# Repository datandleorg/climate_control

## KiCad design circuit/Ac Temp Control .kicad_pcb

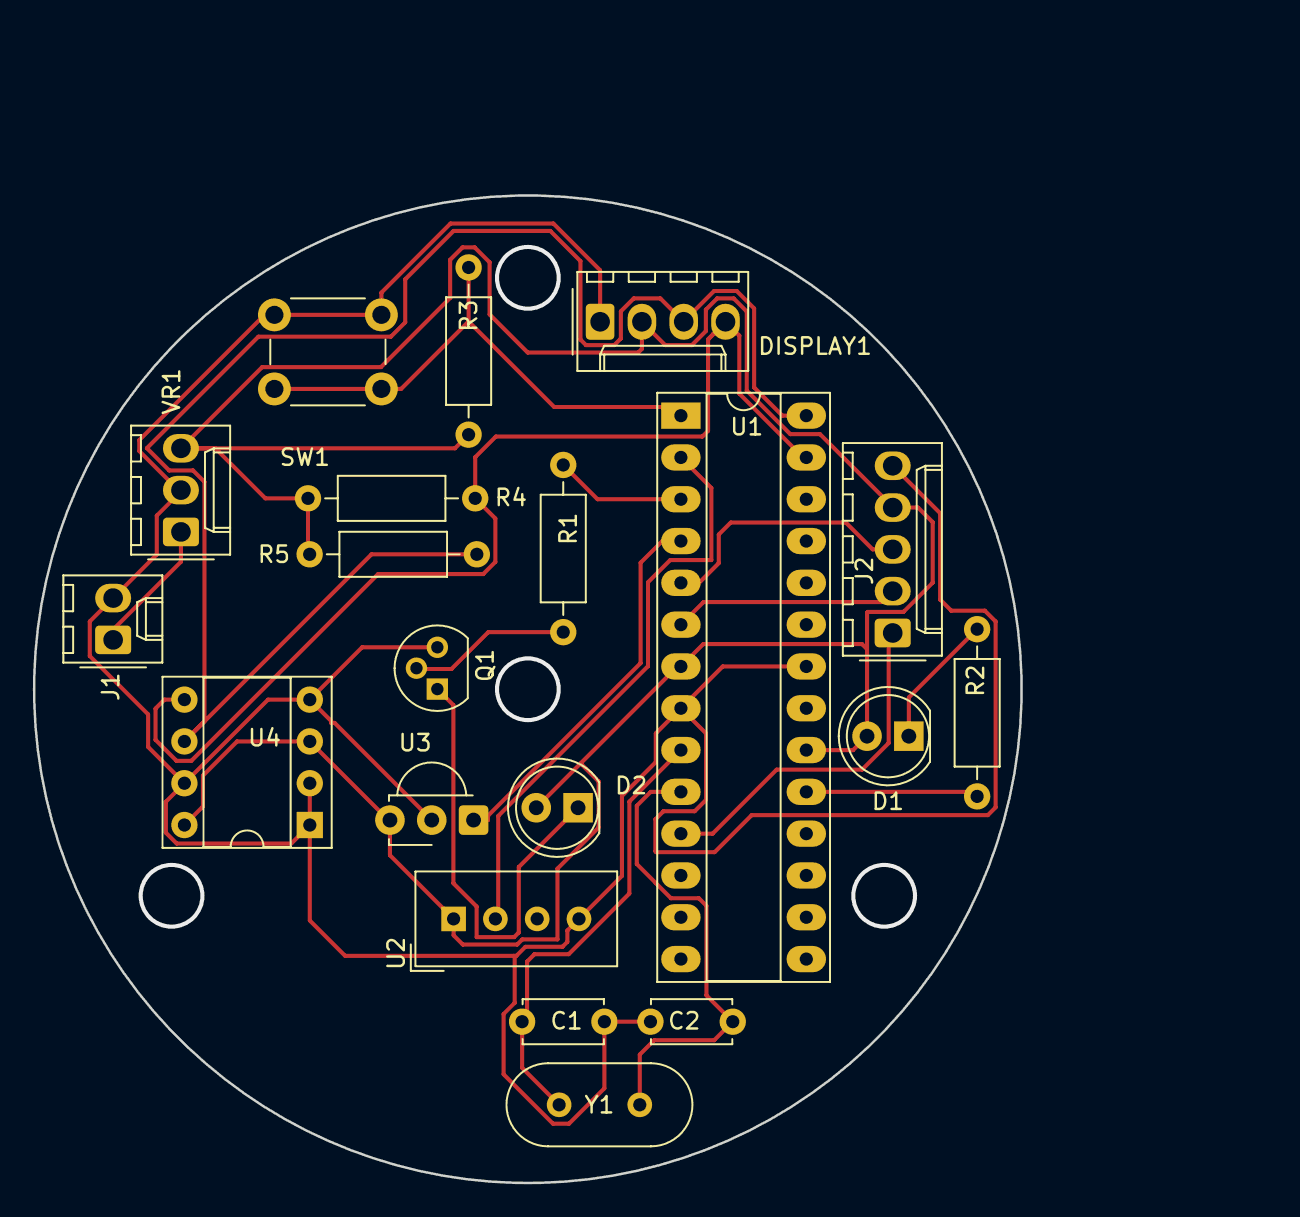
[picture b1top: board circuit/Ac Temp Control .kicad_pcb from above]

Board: 2 copper layers, 74.8 x 69.8 mm, 20 parts (0 on the bottom side), 18 nets.

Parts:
C1, C2: 22UF; C_Disc_D4.7mm_W2.5mm_P5.00mm
D1: LED; LED_D5.0mm
D2: IR_EMITTER; LED_D5.0mm
DISPLAY1: SSD1306; Molex_KK-254_AE-6410-04A_1x04_P2.54mm_Vertical
J1: Conn_01x02_Male; Molex_KK-254_AE-6410-02A_1x02_P2.54mm_Vertical
J2: Conn_01x05_Male; Molex_KK-254_AE-6410-05A_1x05_P2.54mm_Vertical
Q1: P2N2222A; TO-92
R1: 470; R_Axial_DIN0207_L6.3mm_D2.5mm_P10.16mm_Horizontal
R2, R3: 100; R_Axial_DIN0207_L6.3mm_D2.5mm_P10.16mm_Horizontal
R4, R5: 4.7k; R_Axial_DIN0207_L6.3mm_D2.5mm_P10.16mm_Horizontal
SW1: SW_Push; SW_PUSH_6mm
U1: ATmega328-P; DIP-28_W7.62mm_Socket_LongPads
U2: DHT11; Aosong_DHT11_5.5x12.0_P2.54mm
U3: TSOP382xx; Vishay_MINICAST-3Pin
U4: CAT24C256; DIP-8_W7.62mm_Socket
VR1: L7805; Molex_KK-254_AE-6410-03A_1x03_P2.54mm_Vertical
Y1: 16MHZ; Crystal_HC18-U_Vertical

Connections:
GND: C1.2, C2.2, DISPLAY1.1 (GND), J1.2, J2.5, Q1.3 (E), SW1.1, U1.8 (GND), U1.22 (GND), U2.4 (GND), U3.2 (GND), U4.1 (A0), U4.2 (A1), U4.4 (GND), U4.7 (WP), VR1.2 (GND)
unnamed: C1.1, U1.9 (XTAL1/PB6), Y1.1
unnamed: C2.1, U1.10 (XTAL2/PB7), Y1.2
unnamed: D1.1 (K), R2.1
unnamed: D1.2 (A), D2.2, DISPLAY1.2 (VCC), J2.4, R3.2, R4.2, R5.2, U1.7 (VCC), U1.20 (AVCC), U2.1 (VCC), U3.3 (Vs), U4.3 (A2), U4.8 (VCC), VR1.3 (OUT)
unnamed: D2.1, Q1.1 (C)
unnamed: DISPLAY1.3 (SCL), R5.1, U1.28 (PC5), U4.6 (SCL)
unnamed: DISPLAY1.4 (SDA), R4.1, U1.27 (PC4), U4.5 (SDA)
unnamed: J1.1, VR1.1 (IN)
unnamed: J2.1, U1.11 (PD5)
unnamed: J2.2, U1.6 (PD4)
unnamed: J2.3, U1.5 (PD3)
unnamed: Q1.2 (B), R1.2
unnamed: R1.1, U1.3 (PD1)
unnamed: R2.2, U1.19 (PB5)
unnamed: R3.1, SW1.2, U1.1 (~RESET/PC6)
unnamed: U1.2 (PD0), U2.2 (IO)
unnamed: U1.4 (PD2), U3.1 (OUT)

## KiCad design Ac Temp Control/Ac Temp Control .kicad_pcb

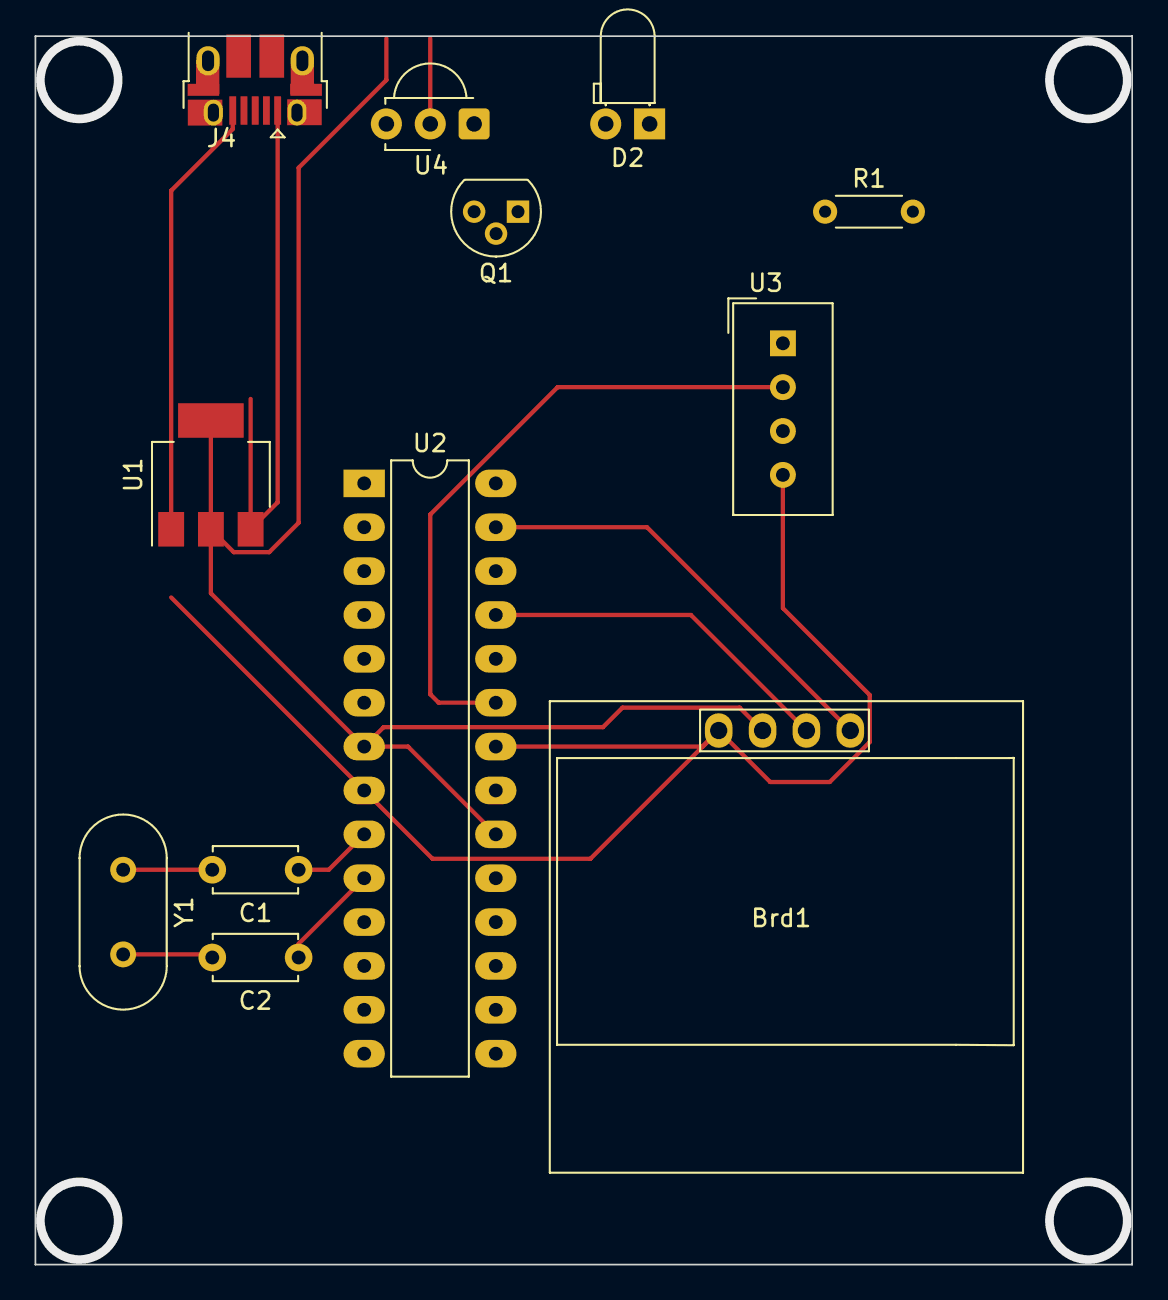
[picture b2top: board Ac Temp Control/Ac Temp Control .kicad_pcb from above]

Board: 2 copper layers, 63.5 x 71.1 mm, 12 parts (0 on the bottom side), 13 nets.

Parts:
Brd1: SSD1306; 128x64OLED
C1, C2: 22UF-0805-6.3V-20%; C_Disc_D4.7mm_W2.5mm_P5.00mm
D2: LED-IRSIDE_EMITTER; LED_D3.0mm_Horizontal_O1.27mm_Z2.0mm_IRGrey
J4: USB_B_Micro; USB_Micro-B_Amphenol_10103594-0001LF_Horizontal
Q1: TRANS_NPN-P2N2222A; TO-92
R1: 470; R_Axial_DIN0204_L3.6mm_D1.6mm_P5.08mm_Horizontal
U1: AMS1117-5.0; SOT-223-3_TabPin2
U2: ATmega328-P; DIP-28_W7.62mm_LongPads
U3: DHT11; Aosong_DHT11_5.5x12.0_P2.54mm
U4: TSOP382xx; Vishay_MINICAST-3Pin
Y1: CRYSTAL-16MHZPTH-HC49US; Crystal_HC18-U_Vertical

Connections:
GND: Brd1.1 (GND), J4.5 (GND), Q1.3 (E), U1.1 (GND), U2.8 (GND), U2.22 (GND), U3.4 (GND), U4.2 (GND)
unnamed: Brd1.2 (VCC), U1.2 (VO), U2.7 (VCC), U2.20 (AVCC), U3.1 (VCC), U4.3 (Vs)
unnamed: Brd1.3 (SCL), U2.25 (PC2)
unnamed: Brd1.4 (SDA), U2.27 (PC4)
unnamed: C1.1, U2.9 (XTAL1/PB6)
unnamed: C1.2, Y1.1
unnamed: C2.1, U2.10 (XTAL2/PB7)
unnamed: C2.2, Y1.2
unnamed: J4.1 (VBUS), U1.3 (VI)
unnamed: Q1.2 (B), R1.2
unnamed: R1.1, U2.4 (PD2)
unnamed: U2.5 (PD3), U4.1 (OUT)
unnamed: U2.23 (PC0), U3.2 (IO)

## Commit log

2022-10-12 test
2022-10-17 PCB design and Gerber file generation
2022-10-19 Version 2 with 0.6mm track width and clearance made. gerber file generated
2022-10-30 Bug removed and updated gerber files
